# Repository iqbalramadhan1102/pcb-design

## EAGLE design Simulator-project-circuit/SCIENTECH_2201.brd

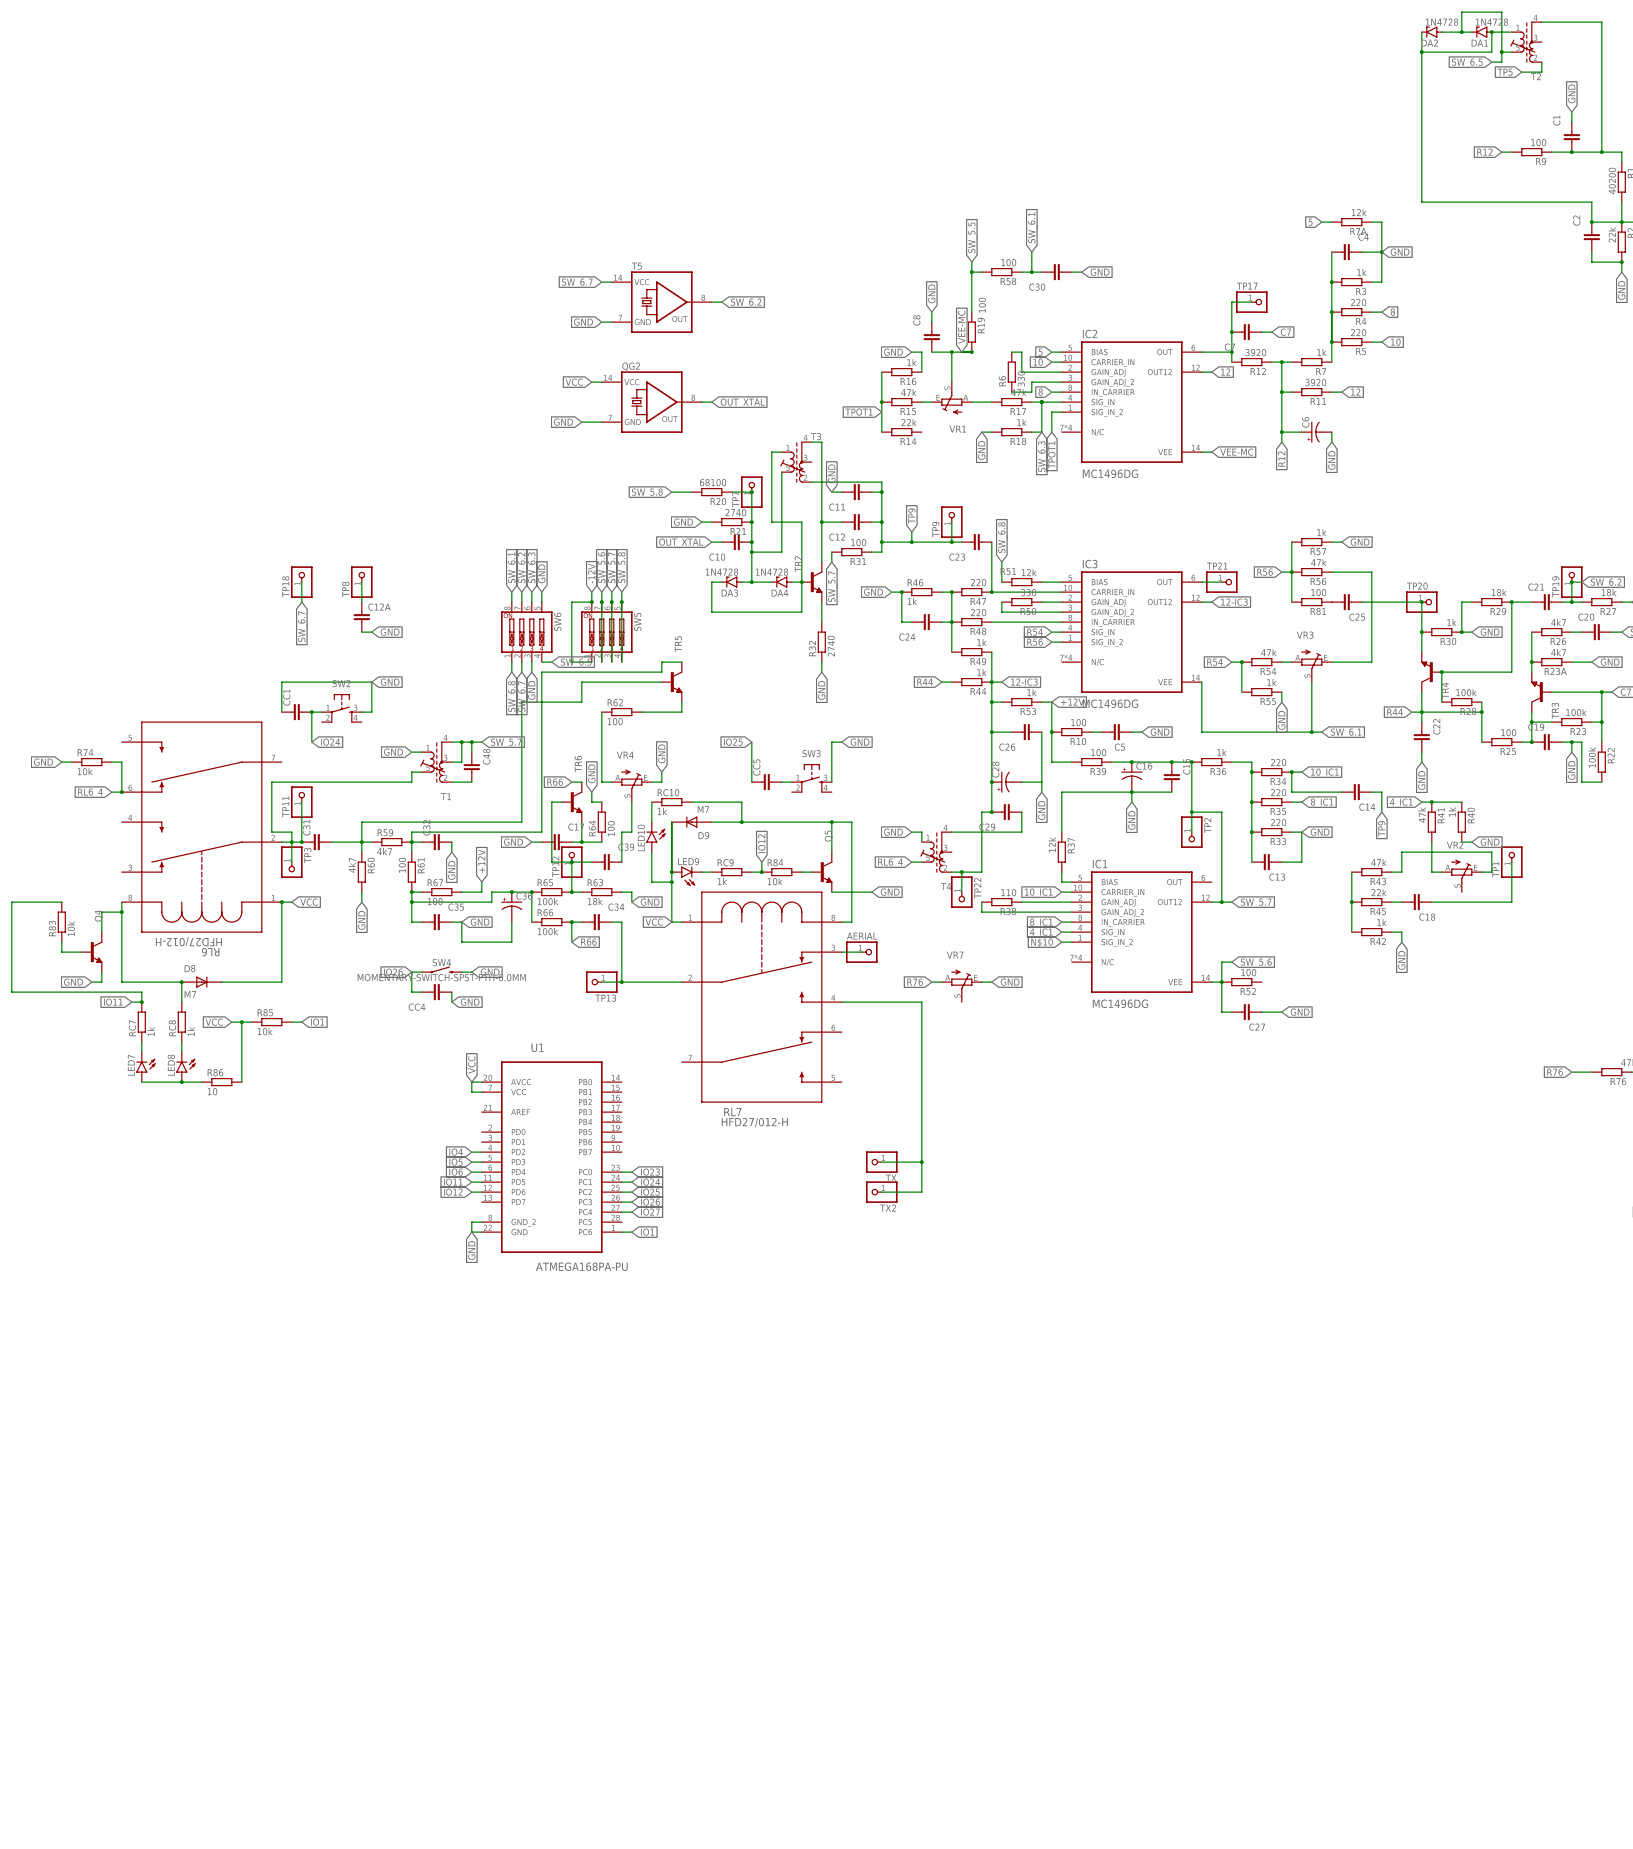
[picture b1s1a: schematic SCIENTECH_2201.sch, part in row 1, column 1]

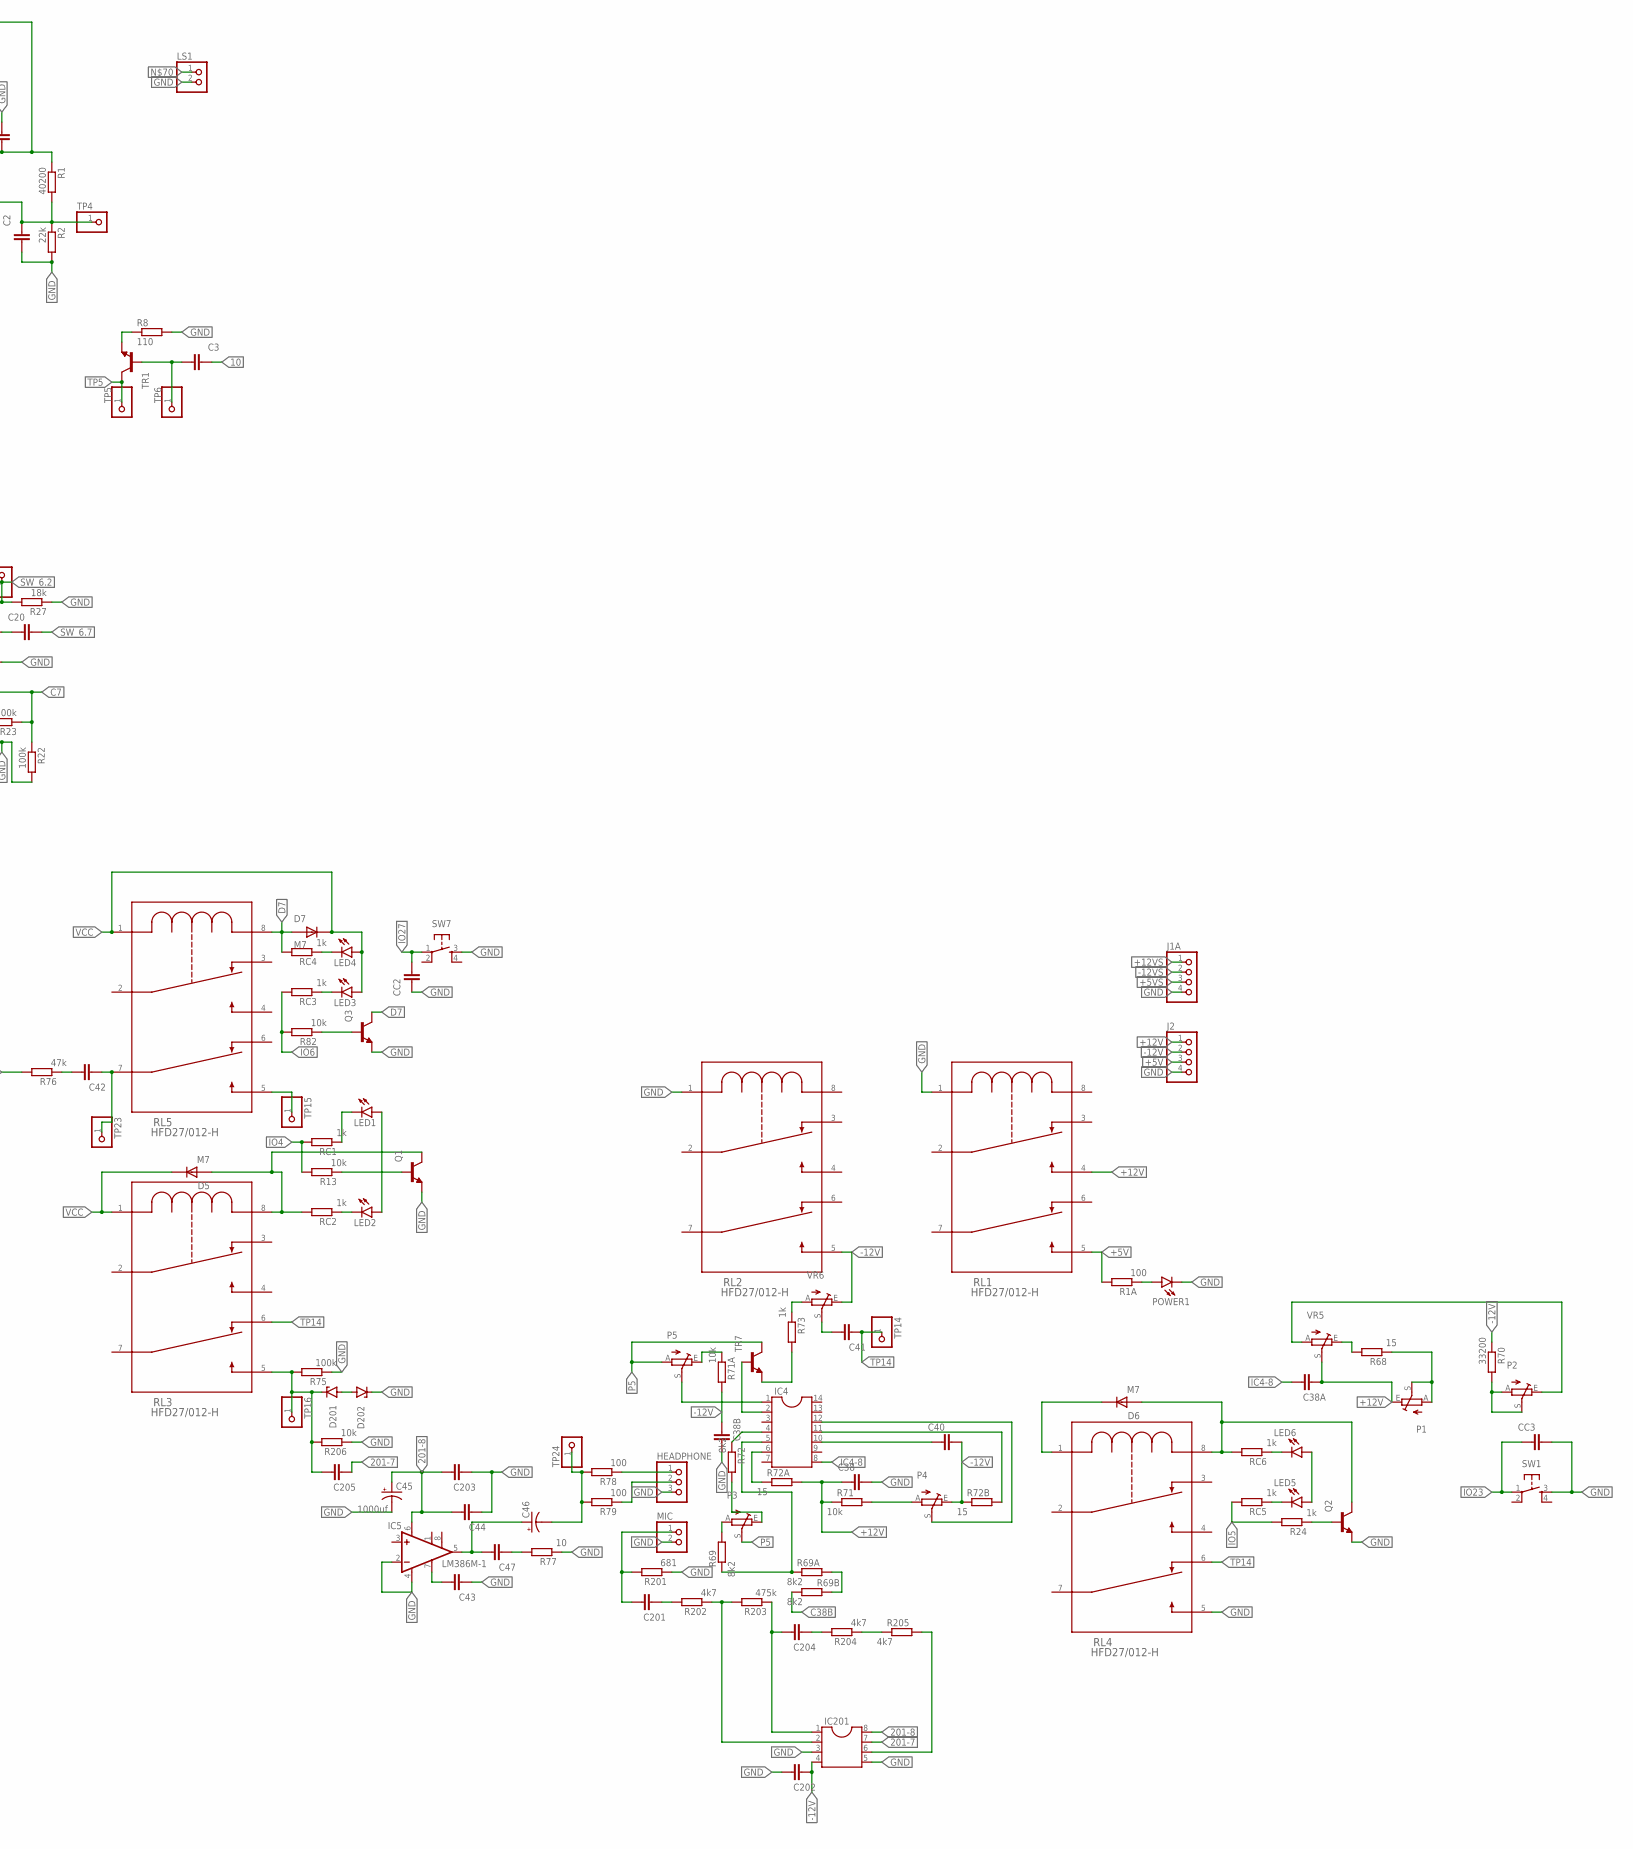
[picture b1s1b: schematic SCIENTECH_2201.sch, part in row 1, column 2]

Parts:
AERIAL: PINHD-1X1; 1X01
C1, C2, C3, C4, C5, C7, C8, C10, C11, C12, C12A, C13, C14, C15, C17, C18, C19, C20, C21, C22, C23, C24, C25, C26, C27, C29, C30, C31, C32, C34, C35, C38, C38A, C38B, C39, C40, C41, C42, C43, C44, C47, C48, C201, C202, C203, C204, C205: C-EUC0805; C0805
C6, C16, C28, C36, C46: CPOL-US153CLV-0405; 153CLV-0405
C45: 1000uf; E5-5
CC1, CC2, CC3, CC4, CC5: C-EUC0805; C0805
D5, D6, D7, D8, D9: M7; DIOM505270X240
D201, D202: 1N4728; DO41Z10
DA1, DA2, DA3, DA4: 1N4728; DO41Z10
HEADPHONE: PINHD-1X3; 1X03
IC1, IC2, IC3: MC1496DG; SOIC127P600X175-14N
IC4: DIL14
IC5: LM386M-1; SO08
IC201: DIL8S; SOCKET-08
J1A, J2: PINHD-1X4; 1X04
LED1, LED2, LED3, LED4, LED5, LED6, LED7, LED8, LED9, LED10: LED3MM
LS1: PINHD-1X2; 1X02
MIC: PINHD-1X2; 1X02
P1, P2, P3, P4, P5: TRIM_EU-CA6V; CA6V
POWER1: LED3MM
Q1, Q2, Q3, Q4, Q5: 1F; SOT23
QG2: QG5860; DIL14S
R1: 40200; R0805
R1A, R9, R10, R19, R25, R31, R39, R52, R58, R61, R62, R64, R67, R78, R79, R81: 100; R0805
R2, R14, R45: 22k; R0805
R3, R7, R16, R18, R24, R30, R36, R40, R42, R44, R46, R49, R53, R55, R57, R73: 1k; R0805
R4, R5, R33, R34, R35, R47, R48: 220; R0805
R6, R50: 330; R0805
R7A, R37, R51: 12k; R0805
R8, R38: 110; R0805
R11, R12: 3920; R0805
R13, R71, R71A, R74, R82, R83, R84, R85, R206: 10k; R0805
R15, R17, R41, R43, R54, R56, R76: 47k; R0805
R20: 68100; R0805
R21, R32: 2740; R0805
R22, R23, R28, R65, R66, R75: 100k; R0805
R23A, R26, R59, R60, R202, R204, R205: 4k7; R0805
R27, R29, R63: 18k; R0805
R68, R72A, R72B: 15; R0805
R69, R69A, R69B, R72: 8k2; R0805
R70: 33200; R0805
R77, R86: 10; R0805
R201: 681; R0805
R203: 475k; R0805
RC1, RC2, RC3, RC4, RC5, RC6, RC7, RC8, RC9, RC10: 1k; R0805
RL1, RL2, RL3, RL4, RL5, RL6, RL7: HFD27/012-H; RELAY_HFD27_HNG
SW1, SW2, SW3, SW7: TAC_SWITCHPTH; TACTILE-PTH
SW4: MOMENTARY-SWITCH-SPST-PTH-6.0MM; TACTILE_SWITCH_PTH_6.0MM
SW5, SW6: SW_DIP-4; EDG-04
T1, T2, T3, T4: 71-24513-2; 71-5
T5: QG5860; DIL14S
TP1, TP2, TP3, TP4, TP5, TP6, TP7, TP8, TP9, TP11, TP12, TP13, TP14, TP15, TP16, TP17, TP18, TP19, TP20, TP21, TP22, TP23, TP24: PINHD-1X1; 1X01
TR1, TR2, TR3, TR4, TR5, TR6, TR7: 1AM; SOT23
TX, TX2: PINHD-1X1; 1X01
U1: ATMEGA168PA-PU; DIP254P762X457-28
VR1, VR2, VR3, VR4, VR5, VR6, VR7: TRIM_EU-PT10S; PT-10S

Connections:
4_IC1: IC1.4 (SIG_IN), R40.1, R41.1
5: IC2.5 (BIAS), R7A.2
8: IC2.8 (IN_CARRIER), R4.1
8_IC1: IC1.8 (IN_CARRIER), R35.1
10: C3.2, IC2.10 (CARRIER_IN), R5.1
10_IC1: C14.2, IC1.10 (CARRIER_IN), R34.1
12: IC2.12 (OUT12), R11.1
12-IC3: C26.2, C28.+, C29.2, IC3.12 (OUT12), R44.1, R49.1, R53.2, T4.2 (A1), TP22.1
201-7: C205.1, IC201.7
201-8: C44.2, C45.+, C203.2, IC5.6 (VS), IC201.8
+5V: J2.3, R1A.2, RL1.5 (3)
+5VS: J1A.3
+12V: C38.1, C38A.1, J2.1, P1.E, R10.2, R39.2, R53.1, R67.2, R71.1, R72A.2, RL1.4, VR5.S
+12VS: J1A.1
-12V: C38B.1, C40.2, C202.1, IC201.4, J2.2, P4.E, R70.1, R71A.2, R72B.1, RL2.5 (3), SW5.1, SW5.8, VR6.E
-12VS: J1A.2
C7: C7.1, R22.1, R23.1, TR3.1 (B)
C38B: R69B.1
D7: D7.A, Q3.3 (C), RC4.2, RL5.8 (2)
GND: C1.2, C2.1, C4.2, C5.1, C6.-, C8.2, C11.2, C12A.2, C13.1, C15.2, C16.-, C17.1, C19.2, C22.2, C24.2, C26.1, C27.1, C28.-, C30.1, C32.2, C35.2, C36.-, C38.2, C38B.2, C43.1, C44.1, C45.-, C202.2, C203.1, CC1.1, CC2.1, CC3.2, CC4.1, D202.C, HEADPHONE.3, IC5.2 (-IN), IC5.4 (GND), IC201.3, IC201.5, J1A.4, J2.4, LS1.2, MIC.2, POWER1.K (C), Q1.2 (E), Q2.2 (E), Q3.2 (E), Q4.2 (E), Q5.2 (E), QG2.7 (GND), R2.2, R3.1, R7A.1, R8.2, R16.1, R18.2, R21.2, R22.2, R23A.1, R27.1, R29.2, R30.1, R32.1, R33.1, R37.1, R40.2, R42.1, R46.1, R55.1, R57.1, R60.2, R63.2, R64.2, R74.1, R75.1, R77.1, R201.1, R206.1, RL1.1, RL2.1, RL4.5 (3), SW1.3, SW2.3, SW3.3, SW4.3 (2), SW6.3, SW6.5, SW7.3, T1.1 (E2), T4.1 (E2), T5.7 (GND), U1.8 (GND_2), U1.22 (GND), VR4.E, VR7.E
IC4-8: C38A.2, IC4.8
IO1: R85.2, U1.1 (PC6)
IO4: R13.2, RC1.2, U1.4 (PD2)
IO5: R24.2, RC5.2, U1.5 (PD3)
IO6: R82.2, RC3.2, U1.6 (PD4)
IO11: R83.2, RC7.2, U1.11 (PD5)
IO12: R84.1, RC9.2, U1.12 (PD6)
IO23: CC3.1, SW1.1, U1.23 (PC0)
IO24: CC1.2, SW2.1, U1.24 (PC1)
IO25: CC5.1, U1.25 (PC2)
IO26: CC4.2, SW4.1, U1.26 (PC3)
IO27: CC2.2, SW7.1, U1.27 (PC4)
unnamed: LED7.A, LED8.A, R86.1
unnamed: LED7.K (C), RC7.1
unnamed: LED8.K (C), RC8.1
unnamed: D8.A, Q4.3 (C), RC8.2, RL6.8 (2)
unnamed: C48.2, T1.2 (A1)
unnamed: D9.A, Q5.3 (C), RC10.2, RL7.8 (2)
unnamed: C31.2, R59.1, R60.1, TR5.1 (B)
unnamed: C32.1, R59.2, R61.1, TR5.3 (C)
unnamed: C5.2, R10.1
unnamed: C39.1, R63.1, R65.2, TP12.1, TR6.1 (B)
unnamed: RL7.4, TX.1, TX2.1
unnamed: C34.2, RL7.2 (3_2), TP13.1
unnamed: LED9.K (C), RC9.1
unnamed: LED10.K (C), RC10.1
unnamed: Q5.1 (B), R84.2
unnamed: AERIAL.1, RL7.3 (5)
unnamed: CC5.2, SW3.1
unnamed: Q4.1 (B), R83.1
unnamed: IC2.3 (GAIN_ADJ_2), R6.1
unnamed: IC2.2 (GAIN_ADJ), R6.2
unnamed: R17.2, VR1.A
unnamed: R15.1, VR1.E
unnamed: C21.1, R28.2, R29.1, TR4.1 (B)
unnamed: C7.2, IC2.6 (OUT), R12.2, TP17.1
unnamed: C29.1, T4.4 (E1)
unnamed: C4.1, R3.2, R4.2, R5.2, R7.1
unnamed: IC3.2 (GAIN_ADJ), R50.1
unnamed: IC3.3 (GAIN_ADJ_2), R50.2
unnamed: IC3.6 (OUT), TP21.1
unnamed: IC3.5 (BIAS), R51.1
unnamed: IC3.8 (IN_CARRIER), R48.1
unnamed: C23.1, IC3.10 (CARRIER_IN), R47.1
unnamed: C24.1, R46.2, R47.2, R48.2, R49.2
unnamed: C12.2, T3.4 (E1), TR2.3 (C)
unnamed: R32.2, TR2.2 (E)
unnamed: DA3.C, DA4.A, T3.1 (E2), TR2.1 (B)
unnamed: C10.1, DA3.A, DA4.C, R20.1, R21.1, T3.5 (A2), TP7.1
unnamed: C25.2, R81.1
unnamed: R54.1, VR3.A
unnamed: R56.1, VR3.E
unnamed: C25.1, R30.2, TP20.1, TR4.2 (E)
unnamed: IC1.2 (GAIN_ADJ), R38.1
unnamed: C19.1, R23.2, R25.1, TR3.3 (C)
unnamed: C13.2, R33.2, R34.2, R35.2, R36.1
unnamed: R23A.2, R26.2, TR3.2 (E)
unnamed: C20.1, R26.1
unnamed: IC1.3 (GAIN_ADJ_2), R38.2
unnamed: R42.2, R43.2, R45.2
unnamed: C18.2, R45.1
unnamed: R43.1, VR2.E
unnamed: C18.1, TP1.1
unnamed: R41.2, VR2.A
unnamed: IC1.5 (BIAS), R37.2
unnamed: C39.2, VR4.S
unnamed: C1.1, R1.1, R9.1, T2.4 (E1)
unnamed: R8.1, TR1.2 (E)
unnamed: C3.1, TP6.1, TR1.1 (B)
unnamed: C12A.1, TP8.1
unnamed: LED4.K (C), RC4.1
unnamed: LED3.K (C), RC3.1
unnamed: Q3.1 (B), R82.1
unnamed: RL5.5 (3), TP15.1
unnamed: C42.1, RL5.7 (6), TP23.1
unnamed: C42.2, R76.1
unnamed: D5.A, Q1.3 (C), RC2.2, RL3.8 (2)
unnamed: LED1.A, LED2.A
unnamed: LED1.K (C), RC1.1
unnamed: LED2.K (C), RC2.1
unnamed: Q1.1 (B), R13.1
unnamed: C205.2, D201.C, R75.2, R206.2, RL3.5 (3), TP16.1
unnamed: D201.A, D202.A
unnamed: C46.+, C47.2, IC5.5 (OUT)
unnamed: POWER1.A, R1A.1
unnamed: C43.2, IC5.7 (BYPASS)
unnamed: C47.1, R77.2
unnamed: C46.-, R78.2, R79.2, TP24.1
unnamed: HEADPHONE.1, R78.1
unnamed: HEADPHONE.2, R79.1
unnamed: C201.2, MIC.1, R201.2
unnamed: C201.1, R202.2
unnamed: IC201.2, R202.1, R203.2
unnamed: C204.2, IC201.1, R203.1
unnamed: C204.1, R204.2
unnamed: R204.1, R205.1
unnamed: P2.A, P2.S, R70.2
unnamed: IC201.6, R205.2
unnamed: C41.2, VR6.S
unnamed: R73.1, VR6.A
unnamed: R73.2, TR7.2 (E)
unnamed: R69A.2, R69B.2
unnamed: P5.E, R71A.1
unnamed: IC4.2, TR7.1 (B)
unnamed: IC4.1, P5.S
unnamed: IC4.6, R72A.1
unnamed: IC4.4, R72.1
unnamed: P3.E, R72.2
unnamed: P3.A, R69.2
unnamed: IC4.5, R69.1, R69A.1
unnamed: D6.C, RL4.1
unnamed: P4.A, R71.2
unnamed: R68.2, VR5.E
unnamed: IC4.11, R72B.2
unnamed: C40.1, IC4.10
unnamed: IC4.12, P4.S
unnamed: D6.A, Q2.3 (C), RC6.2, RL4.8 (2)
unnamed: P1.A, P1.S, R68.1
unnamed: LED6.K (C), RC6.1
unnamed: LED5.A, LED6.A
unnamed: LED5.K (C), RC5.1
unnamed: P2.E, VR5.A
unnamed: Q2.1 (B), R24.1
unnamed: C2.2, DA1.A, DA2.C, R1.2, R2.1, T2.1 (E2), TP4.1
unnamed: R62.1, VR4.A
unnamed: R62.2, TR5.2 (E)
unnamed: C17.2, R64.1, TR6.2 (E)
OUT_XTAL: C10.2, QG2.8 (OUT)
P5: P3.S, P5.A, TR7.3 (C)
R12: C6.+, R7.2, R9.2, R11.2, R12.1
R44: C22.1, R25.2, R28.1, R44.2, TR4.3 (C)
R54: IC3.4 (SIG_IN), R54.2, R55.2
R56: IC3.1 (SIG_IN_2), R56.2, R57.2, R81.2
R66: C34.1, R66.2, TR6.3 (C)
R67: C35.1, C36.+, R61.2, R65.1, R66.1, R67.1
R76: R76.2, VR7.A
RL6_4: R74.2, RL6.6 (8), T4.5 (A2)
SW_5.5: R19.1, R58.2
SW_5.6: C27.2, IC1.14 (VEE), R52.2, SW5.2, SW5.7
SW_5.7: C15.1, C16.+, C48.1, IC1.12 (OUT12), R31.2, R36.2, R39.1, SW5.3, SW5.6, T1.3 (Z), T1.4 (E1), TP2.1
SW_5.8: R20.2, SW5.4, SW5.5
SW_6.1: C30.2, IC3.14 (VEE), R58.1, SW6.8, VR3.S
SW_6.2: C21.2, R27.2, SW6.7, T5.8 (OUT), TP19.1
SW_6.3: IC2.4 (SIG_IN), R17.1, R18.1, SW6.6
SW_6.5: DA1.C, DA2.A, SW6.4, T2.5 (A2)
SW_6.7: C20.2, SW6.2, T5.14 (VCC), TP18.1
SW_6.8: R51.2, SW6.1
TP3: C31.1, RL6.2 (3_2), T1.5 (A2), TP3.1, TP11.1
TP5: T2.2 (A1), TP5.1, TR1.3 (C)
TP9: C11.1, C12.1, C14.1, C23.2, R31.1, T3.2 (A1), TP9.1
TP14: C41.1, RL3.6 (8), RL4.6 (8), TP14.1
TPOT1: IC2.1 (SIG_IN_2), R14.2, R15.2, R16.2
VCC: D5.C, D7.C, D8.C, D9.C, LED3.A, LED4.A, LED9.A, LED10.A, QG2.14 (VCC), R85.1, R86.2, RL3.1, RL5.1, RL6.1, RL7.1, U1.7 (VCC), U1.20 (AVCC)
VEE-MC: C8.1, IC2.14 (VEE), R19.2, VR1.S

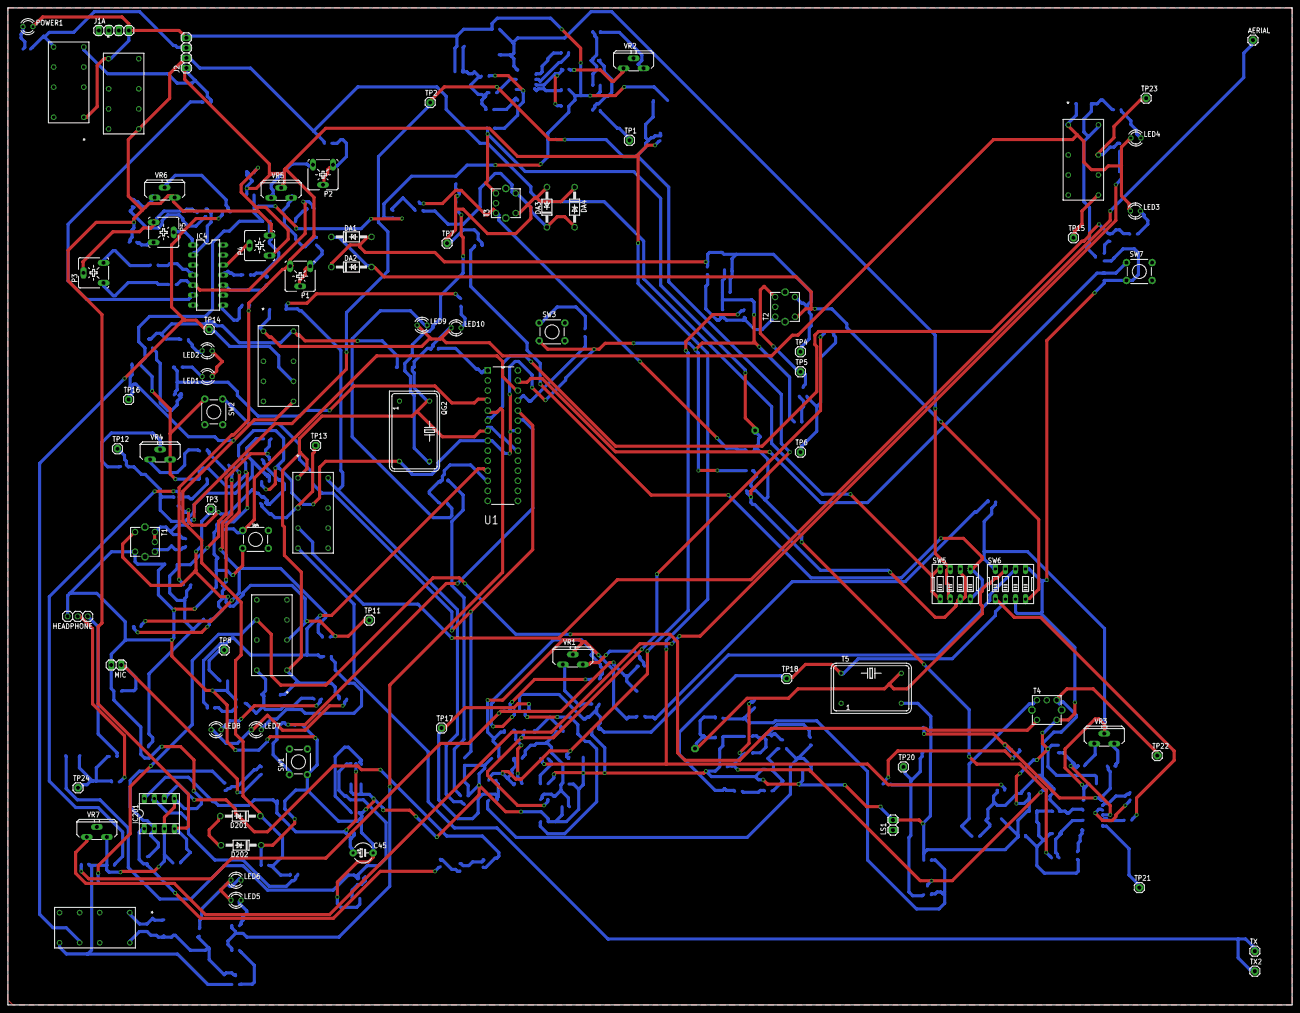
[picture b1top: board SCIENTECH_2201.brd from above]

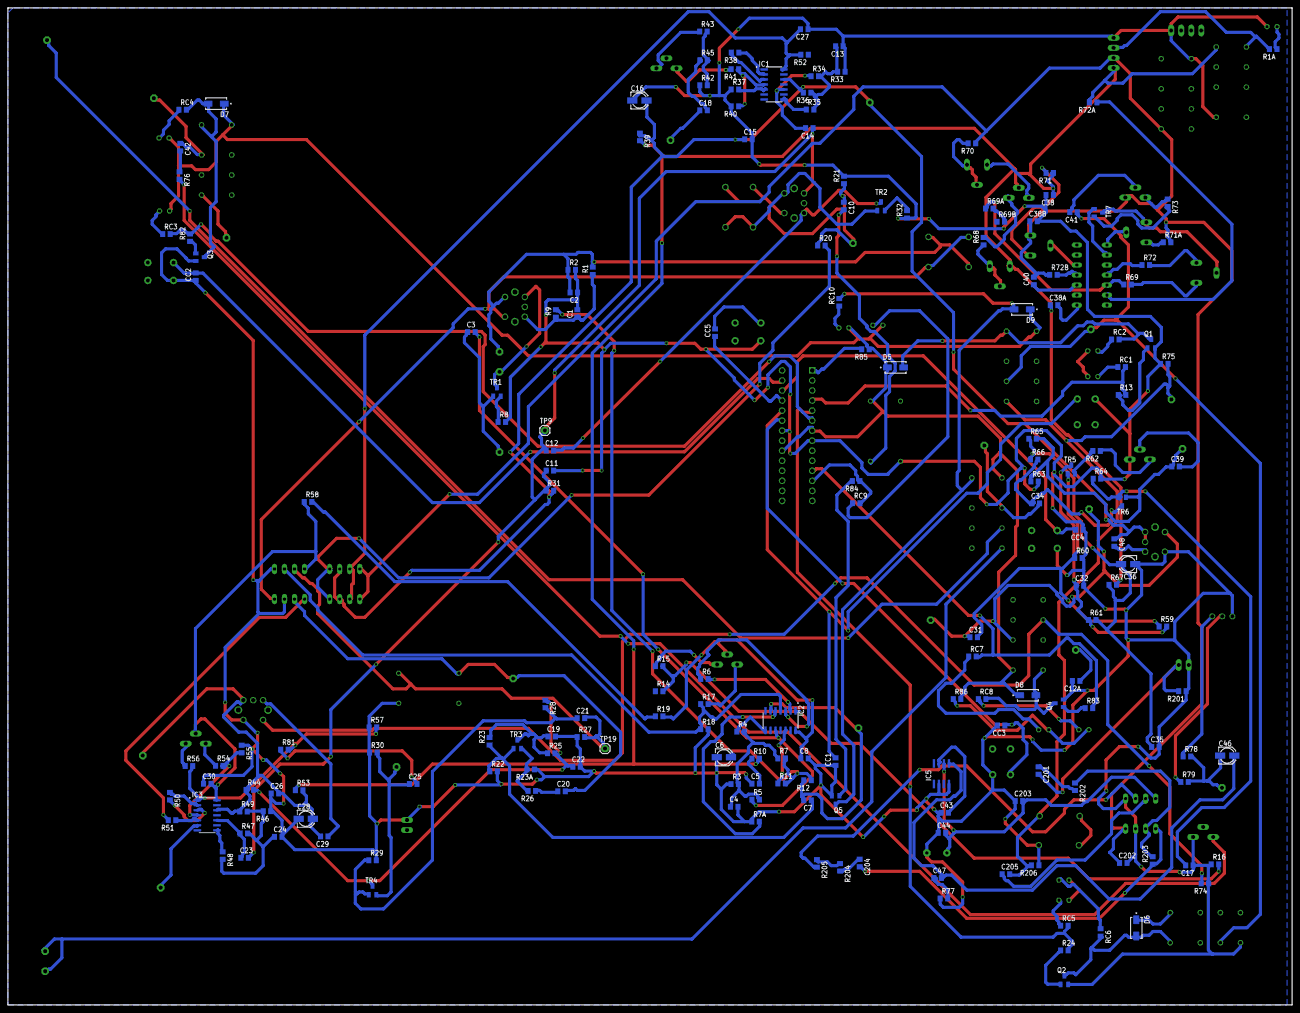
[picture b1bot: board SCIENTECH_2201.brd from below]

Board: 2 copper layers, 325.1 x 252.4 mm, 271 parts (189 on the bottom side), 170 nets.

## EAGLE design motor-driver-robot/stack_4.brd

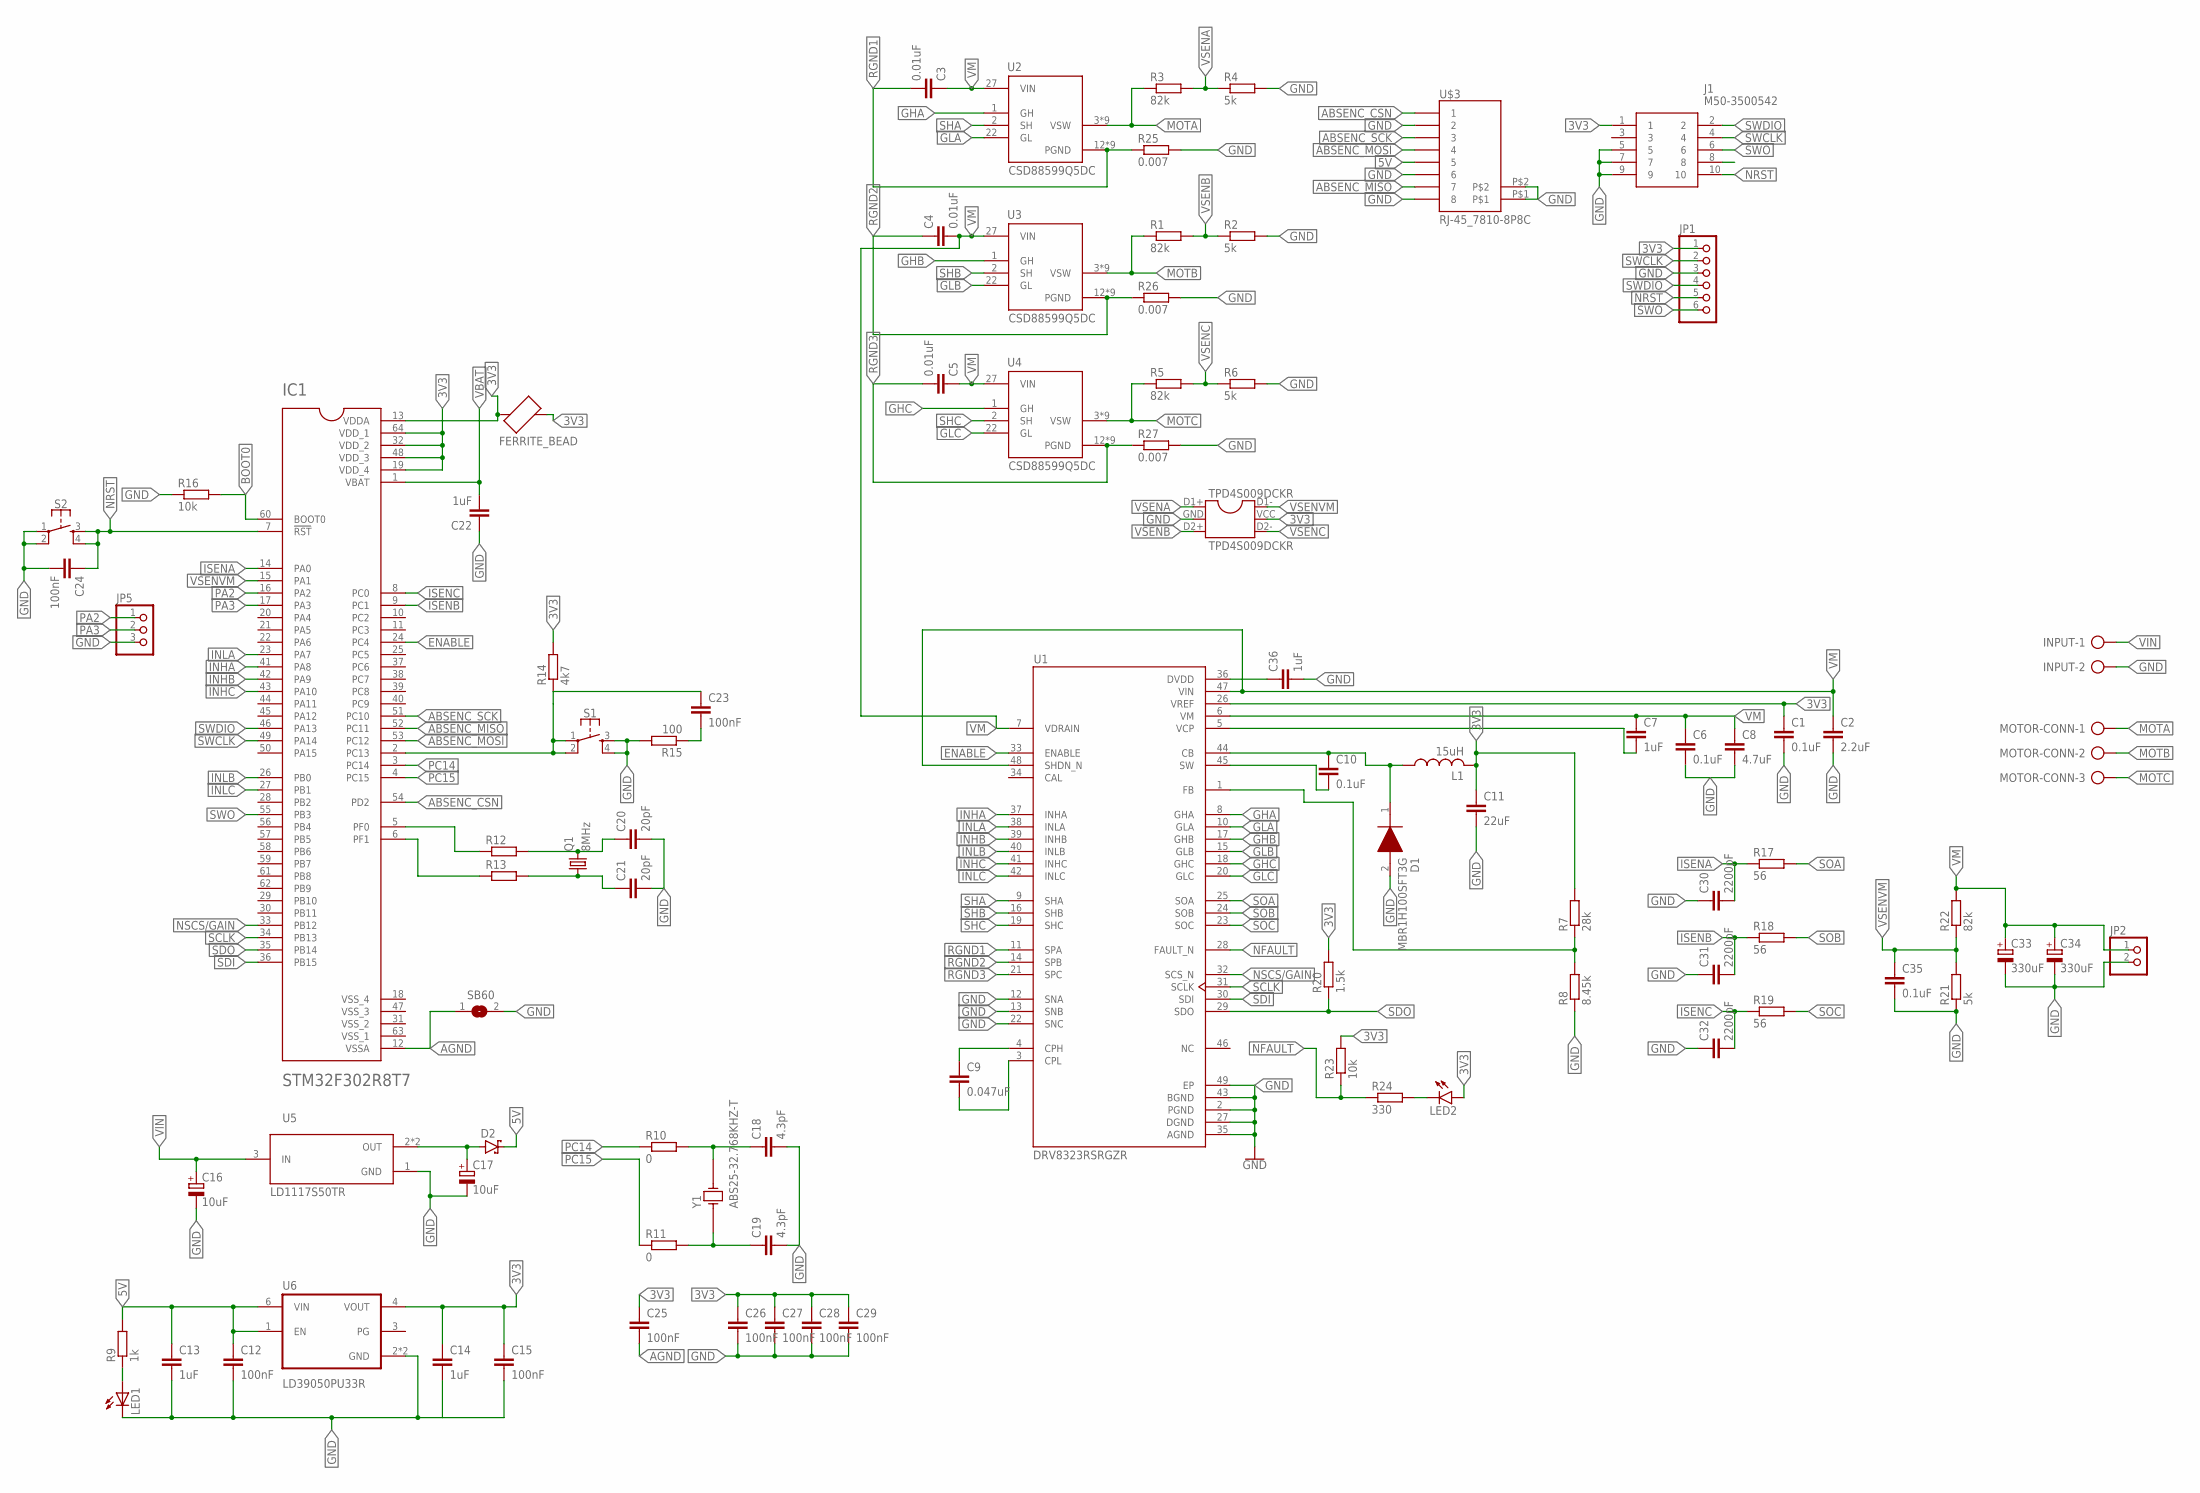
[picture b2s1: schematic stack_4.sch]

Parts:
C1, C6, C10, C35: 0.1uF; C1206
C2: 2.2uF; C0805
C3, C4, C5: 0.01uF; C0805
C7, C36: 1uF; C1206
C8: 4.7uF; C1206
C9: 0.047uF; C0603
C11: 22uF; C1206
C12, C15: 100nF; C1206
C13, C14: 1uF; C0603
C16, C17: 10uF; UD-6,3X5,8_NICHICON
C18, C19: 4.3pF; C025-024X044
C20, C21: 20pF; C025-024X044
C22: 1uF; C0805
C23, C24, C25, C26, C27, C28, C29: 100nF; C0805
C30, C31, C32: 2200pF; C0603
C33, C34: 330uF; UD-10X10_NICHICON
D1: MBR1H100SFT3G; SODFL3616X98N
D2: SCHOTTKY-DIODESMD; SMB
IC1: STM32F302R8T7; QFP50P1200X1200X160-64N
INPUT: AK500/2-H
J1: M50-3500542; M503500542
JP1: PINHD-1X6; 1X06
JP2: PINHD-1X2; 1X02
JP5: PINHD-1X3; 1X03
L1: 15uH; 0805
LED1: LEDCHIP-LED0603; CHIP-LED0603
LED2: LEDSML0805; SML0805
MOTOR-CONN: AK500/3-H
Q1: 8MHz; HC49UP
R1, R3, R5, R22: 82k; R0805
R2, R4, R6, R21: 5k; R0603
R7: 28k; R0805
R8: 8.45k; R0805
R9: 1k; R0805
R10, R11: 0; R0805
R12, R13: R-EU_R0805; R0805
R14: 4k7; R0805
R15: 100; R0805
R16, R23: 10k; R0805
R17, R18, R19: 56; R0603
R20: 1.5k; R0805
R24: 330; R0805
R25, R26, R27: 0.007; R2512
S1, S2: MOMENTARY-SWITCH-SPST-2-SMD-5.2MM; TACTILE_SWITCH_SMD_5.2MM
SB60: SJW
U1: DRV8323RSRGZR; QFN50P700X700X100-49N
U2, U3, U4: CSD88599Q5DC; MOSFET_CSD88599Q5DC
U5: LD1117S50TR; SOT230P700X180-4N
U6: LD39050PU33R; SON95P300X300X100-7N
U$1: TPD4S009DCKR
U$2: FERRITE_BEAD; RESC0603X26N
U$3: RJ-45_7810-8P8C
Y1: ABS25-32.768KHZ-T; XTAL_ABS25-32.768KHZ-6-1-T

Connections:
3V3: C1.1, C11.1, C14.1, C15.1, C25.1, C26.1, C27.1, C28.1, C29.1, IC1.13 (VDDA), IC1.19 (VDD_4), IC1.32 (VDD_2), IC1.48 (VDD_3), IC1.64 (VDD_1), J1.1, JP1.1, L1.2, LED2.A, R7.2, R14.2, R20.2, R23.2, U1.26 (VREF), U6.4 (VOUT), U$1.VCC, U$2.1, U$2.2
5V: C12.1, C13.1, D2.C, R9.2, U6.1 (EN), U6.6 (VIN), U$3.5
ABSENC_CSN: IC1.54 (PD2), U$3.1
ABSENC_MISO: IC1.52 (PC11), U$3.7
ABSENC_MOSI: IC1.53 (PC12), U$3.4
ABSENC_SCK: IC1.51 (PC10), U$3.3
AGND: C25.2, IC1.12 (VSSA), SB60.1
BOOT0: IC1.60 (BOOT0), R16.2
ENABLE: IC1.24 (PC4), U1.33 (ENABLE)
GHA: U1.8 (GHA), U2.1 (GH)
GHB: U1.17 (GHB), U3.1 (GH)
GHC: U1.18 (GHC), U4.1 (GH)
GLA: U1.10 (GLA), U2.22 (GL)
GLB: U1.15 (GLB), U3.22 (GL)
GLC: U1.20 (GLC), U4.22 (GL)
GND: C1.2, C2.2, C6.2, C8.2, C11.2, C12.2, C13.2, C14.2, C15.2, C16.-, C17.-, C18.2, C19.2, C20.2, C21.2, C22.1, C24.2, C26.2, C27.2, C28.2, C29.2, C30.1, C31.1, C32.1, C33.-, C34.-, C35.2, C36.2, D1.2 (A), INPUT.2, J1.5, J1.7, J1.9, JP1.3, JP2.2, JP5.3, LED1.C, R2.2, R4.2, R6.2, R8.1, R15.2, R16.1, R21.1, R25.2, R26.2, R27.2, S1.3, S1.4, S2.1, S2.2, SB60.2, U1.2 (PGND), U1.12 (SNA), U1.13 (SNB), U1.22 (SNC), U1.27 (DGND), U1.35 (AGND), U1.43 (BGND), U1.49 (EP), U5.1 (GND), U6.2 (GND), U6.7 (GND), U$1.GND, U$3.2, U$3.6, U$3.8, U$3.P$1, U$3.P$2
INHA: IC1.41 (PA8), U1.37 (INHA)
INHB: IC1.42 (PA9), U1.39 (INHB)
INHC: IC1.43 (PA10), U1.41 (INHC)
INLA: IC1.23 (PA7), U1.38 (INLA)
INLB: IC1.26 (PB0), U1.40 (INLB)
INLC: IC1.27 (PB1), U1.42 (INLC)
ISENA: C30.2, IC1.14 (PA0), R17.1
ISENB: C31.2, IC1.9 (PC1), R18.1
ISENC: C32.2, IC1.8 (PC0), R19.1
MOTA: MOTOR-CONN.1, R3.1, U2.3 (VSW), U2.4 (VSW), U2.5 (VSW), U2.6 (VSW), U2.7 (VSW), U2.8 (VSW), U2.9 (VSW), U2.10 (VSW), U2.11 (VSW)
MOTB: MOTOR-CONN.2, R1.1, U3.3 (VSW), U3.4 (VSW), U3.5 (VSW), U3.6 (VSW), U3.7 (VSW), U3.8 (VSW), U3.9 (VSW), U3.10 (VSW), U3.11 (VSW)
MOTC: MOTOR-CONN.3, R5.1, U4.3 (VSW), U4.4 (VSW), U4.5 (VSW), U4.6 (VSW), U4.7 (VSW), U4.8 (VSW), U4.9 (VSW), U4.10 (VSW), U4.11 (VSW)
unnamed: C9.1, U1.4 (CPH)
unnamed: C7.2, U1.5 (VCP)
unnamed: C9.2, U1.3 (CPL)
unnamed: C10.2, U1.45 (SW)
unnamed: R7.1, R8.2, U1.1 (FB)
unnamed: C10.1, D1.1 (K), L1.1, U1.44 (CB)
unnamed: C17.+, D2.A, U5.2 (OUT), U5.4 (OUT)
unnamed: LED1.A, R9.1
unnamed: C18.1, R10.2, Y1.4
unnamed: C19.1, R11.2, Y1.1
unnamed: IC1.5 (PF0), R12.1
unnamed: IC1.6 (PF1), R13.1
unnamed: C20.1, Q1.2, R12.2
unnamed: C21.1, Q1.1, R13.2
unnamed: C23.1, IC1.2 (PC13), R14.1, S1.1, S1.2
unnamed: C23.2, R15.1
unnamed: LED2.C, R24.2
unnamed: C36.1, U1.36 (DVDD)
NFAULT: R23.1, R24.1, U1.28 (FAULT_N)
NRST: C24.1, IC1.7 (!RST), J1.10, JP1.5, S2.3, S2.4
NSCS/GAIN: IC1.33 (PB12), U1.32 (SCS_N)
PA2: IC1.16 (PA2), JP5.1
PA3: IC1.17 (PA3), JP5.2
PC14: IC1.3 (PC14), R10.1
PC15: IC1.4 (PC15), R11.1
RGND1: C3.2, R25.1, U1.11 (SPA), U2.12 (PGND), U2.13 (PGND), U2.14 (PGND), U2.15 (PGND), U2.16 (PGND), U2.17 (PGND), U2.18 (PGND), U2.19 (PGND), U2.20 (PGND)
RGND2: C4.1, R26.1, U1.14 (SPB), U3.12 (PGND), U3.13 (PGND), U3.14 (PGND), U3.15 (PGND), U3.16 (PGND), U3.17 (PGND), U3.18 (PGND), U3.19 (PGND), U3.20 (PGND)
RGND3: C5.2, R27.1, U1.21 (SPC), U4.12 (PGND), U4.13 (PGND), U4.14 (PGND), U4.15 (PGND), U4.16 (PGND), U4.17 (PGND), U4.18 (PGND), U4.19 (PGND), U4.20 (PGND)
SCLK: IC1.34 (PB13), U1.31 (SCLK)
SDI: IC1.36 (PB15), U1.30 (SDI)
SDO: IC1.35 (PB14), R20.1, U1.29 (SDO)
SHA: U1.9 (SHA), U2.2 (SH)
SHB: U1.16 (SHB), U3.2 (SH)
SHC: U1.19 (SHC), U4.2 (SH)
SOA: R17.2, U1.25 (SOA)
SOB: R18.2, U1.24 (SOB)
SOC: R19.2, U1.23 (SOC)
SWCLK: IC1.49 (PA14), J1.4, JP1.2
SWDIO: IC1.46 (PA13), J1.2, JP1.4
SWO: IC1.55 (PB3), J1.6, JP1.6
VBAT: C22.2, IC1.1 (VBAT)
VIN: C16.+, INPUT.1, U5.3 (IN)
VM: C2.1, C3.1, C4.2, C5.1, C6.1, C7.1, C8.1, C33.+, C34.+, JP2.1, R22.2, U1.6 (VM), U1.7 (VDRAIN), U1.47 (VIN), U1.48 (SHDN_N), U2.27 (VIN), U3.27 (VIN), U4.27 (VIN)
VSENA: R3.2, R4.1, U$1.D1+
VSENB: R1.2, R2.1, U$1.D2+
VSENC: R5.2, R6.1, U$1.D2-
VSENVM: C35.1, IC1.15 (PA1), R21.2, R22.1, U$1.D1-

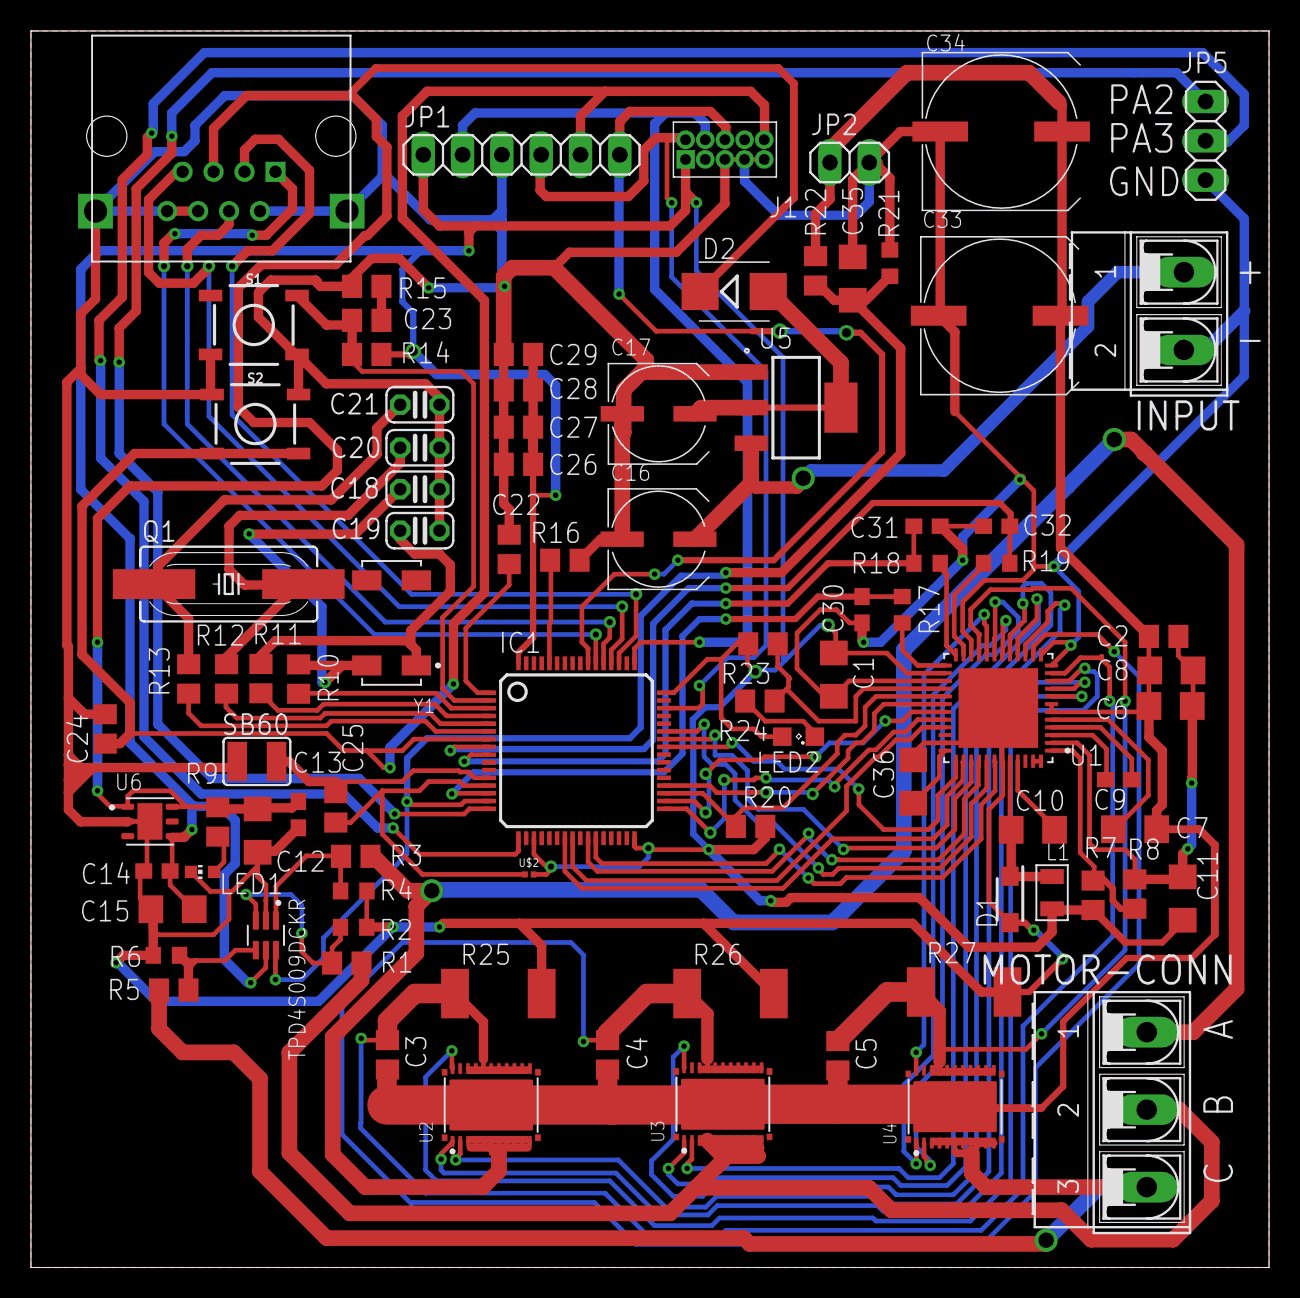
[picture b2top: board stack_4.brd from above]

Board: 2 copper layers, 80.0 x 79.9 mm, 89 parts (0 on the bottom side), 75 nets.

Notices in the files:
parts and their libraries:
SparkFun-Electromechanical: Licensing: Creative Commons ShareAlike 4.0 International - https://creativecommons.org/licenses/by-sa/4.0
COPYRIGHT: Copyright (C) 2023 Ultra Librarian. All rights reserved.
